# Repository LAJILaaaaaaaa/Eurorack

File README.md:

# Eurorack

## 模块尺寸规范
[01] [物理规格参考链接_doepfer](https://www.doepfer.de/a100_man/a100m_e.htm)  
[02] [物理规格参考链接_intellijel](https://intellijel.com/support/1u-technical-specifications/)

## 信号和电压
[电气规格参考链接](https://www.doepfer.de/a100_man/a100t_e.htm)  

### 音频信号  
>通常在10Vpp范围内（从-5V到+5V）。  

### 控制电压  
>由LFO和ADSR等调制源产生，LFO通常从-2.5 V到+2.5 V（5 Vpp），ADSR从0 V到+8 V。

### 触发电压  
>触发器、门或时钟信号，启动过程或功能，是矩形信号，典型电压电平为0/+5 V。在触发应用程序的情况下，通常是用于触发事件的信号的上升边缘。  

## 常用网站

### 模块制造商
- [makenoise](https://www.makenoisemusic.com)
- [instruo](https://www.instruomodular.com)
- [4ms](https://4mscompany.com)
- [mutable-instruments](https://pichenettes.github.io/mutable-instruments-documentation/)
- [busycircuits](https://busycircuits.com)
- [intellijel](https://intellijel.com)
- [expert-sleepers](https://www.expert-sleepers.co.uk)
- [befaco](https://www.befaco.org)
- [Der Mann mit der Maschine](https://shop.dermannmitdermaschine.de) 
- [antumbra](https://www.antumbra.eu)
- [QU-Bit](https://www.qubitelectronix.com/shop)
- [2HP](https://www.twohp.com/modules)
- [musicthing](https://www.musicthing.co.uk)
- [abyssdevices](https://abyssdevices.com)
- [monome](https://monome.org)

### 其他
- [thonk](https://www.thonk.co.uk)
- [modulargrid](https://modulargrid.net)
- [mouser](https://www.mouser.cn)

## 开发者套件
开发者套件的目的是将Eurorack中常用的电路模块化，方便Eurorack开发者们在面包板上进行电路实验。
### [PJ301M-12]()
> 单声道音频输入模块

### [PJ301BM]()
> 单声道音频输入模块

### [KEY_LED]()
> 带led灯的轻触开关模块  

### [KEY]()
> 轻触开关模块

### [LED]()
> LED灯模块

### [ENCODER]()
> 编码器模块

## 常用电路
- ne555时钟发生电路  
- 白噪声发生电路  
- 粉色噪声发生电路
- 采样保持电路  
- 电压比较器电路  
- 门转触发电路  
- 触发转门电路  
- 随机门发生器  
- 门随机跳过电路  
- AR包络发生器电路
- 随机电压发生电路

### LED灯光电路
1. 三极管
2. lm321运算放大器
3. 单led
4. 双led
5. rgb

### 运算放大器电路
1. 同相比例放大
2. 反相比例放大
3. 加法器
4. 电压跟随器

## 硬件驱动库
- OLED
- Key
- Encoder
- LED
- ADC
- DAC
- CAP1214电容触摸
- MAX7219数码管驱动

## 模拟电路
- multisim电路仿真

## PCB绘制
Kicad
- PCB艺术外观

## 合成器电路
### 参考网站

## DSP算法

## 常用开发板
- Stm32
  - f103c8t6
  - f411c8t6
- 树莓派
  - pico
  - 5
  - 4B+
- Arduino
  - nano
  - Uno R4

## 常用硬件
- 基础
  - 电阻
  - 电容  
  - 二极管
    - 1N4148高速开关二极管
    - 肖特基二极管
      - 1N5819HW
      - BAT54SLT1G双肖特基二极管
  - NPN三极管
    - MMBT3904
  - LDO
    - LM1117
    - MCP1703 LDO Vref
  - 磁珠
- 控制
  - 按键
  - 电位器
  - 编码器
- 显示
  - LED灯
  - OLED显示器
    - 0.96英寸（驱动SSD1306）
    - 1.29英寸（驱动CH1115）
    - 1.3英寸
    - 1.54英寸（驱动SSD1306）
    - 2.7英寸
- 输入输出
  - 3.5mm单声道插座
  - type-c插座
- 连接
  - 2.54排针排母
  - 1.27排针排母
  - 跳线帽
  - 11mm，m2铜柱
- 运算放大器
  - TL072
  - TL074
  - MCP6002 R2R
  - MCP6004 R2R
  - OPA4171 四运放
  - OPA2171 双运放
  - LM324 四运放
- ADC
  - ADS1115
- DAC
  - WM8731
  - DAC8564
  - DAC128S085
- 其他
  - LM4040
  - CD4051
  - 74hc595 移位寄存器
  - 74AHCT1G125
  - MAX7219 数码管驱动

## 开源模块存储库

> 存储一些开源的模块资料，防止丢失

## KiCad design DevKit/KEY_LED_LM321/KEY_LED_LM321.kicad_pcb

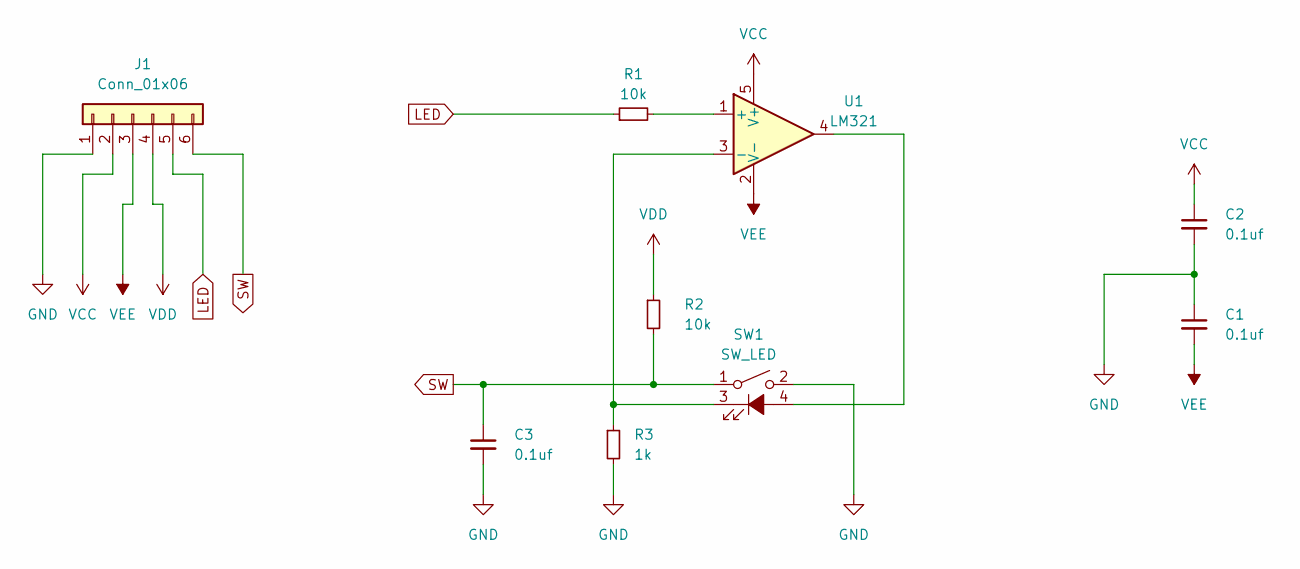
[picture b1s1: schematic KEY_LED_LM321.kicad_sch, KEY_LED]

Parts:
C1, C2, C3: 0.1uf; C_0603_1608Metric
J1: Conn_01x06; PinHeader_1x06_P2.54mm_Vertical
R1, R2: 10k; R_0603_1608Metric
R3: 1k; R_0603_1608Metric
SW1: SW_LED; Button_LED
U1: LM321; SOT-23-5

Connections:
GND: C1.1, C2.2, C3.2, J1.1, R3.2, SW1.2
LED: J1.5, R1.1
unnamed: SW1.4 (A), U1.4
unnamed: R3.1, SW1.3 (K), U1.3 (-)
unnamed: R1.2, U1.1 (+)
SW: C3.1, J1.6, R2.2, SW1.1
VCC: C2.1, J1.2, U1.5 (V+)
VDD: J1.4, R2.1
VEE: C1.2, J1.3, U1.2 (V-)

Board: 2 copper layers, 9 parts (8 on the bottom side), 9 nets, no tracks yet.

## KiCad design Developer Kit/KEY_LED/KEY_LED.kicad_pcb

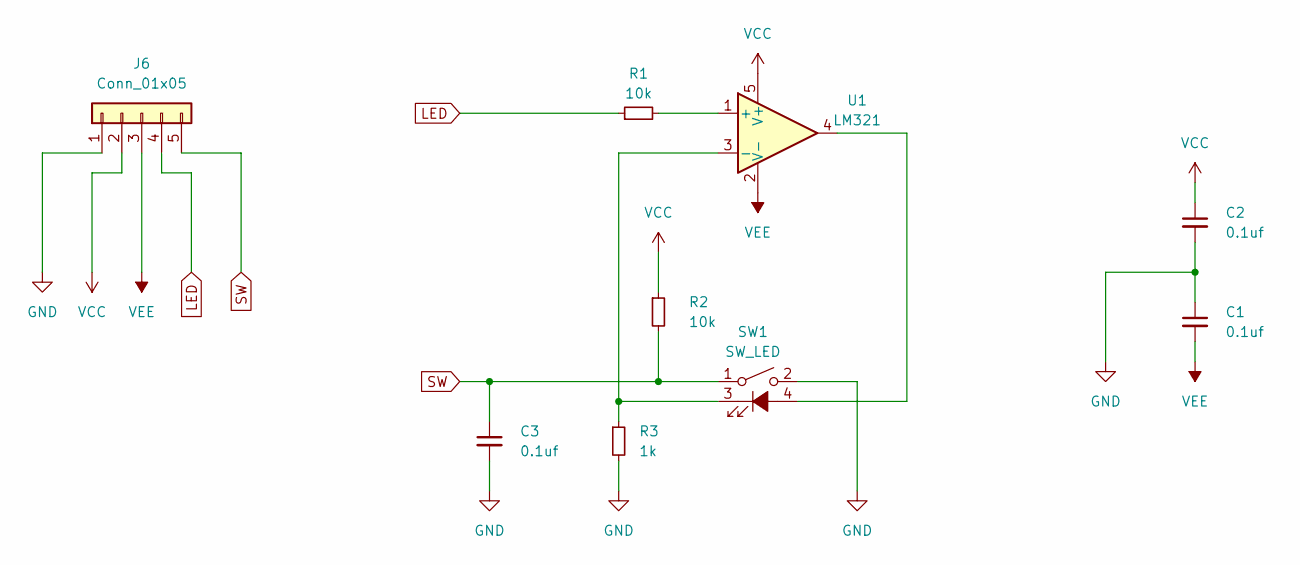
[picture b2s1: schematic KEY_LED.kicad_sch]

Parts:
C1, C2, C3: 0.1uf; C_0603_1608Metric
J6: Conn_01x05; PinHeader_1x05_P2.54mm_Vertical
R1, R2: 10k; R_0603_1608Metric
R3: 1k; R_0603_1608Metric
SW1: SW_LED; Button_LED
U1: LM321; SOT-23-5

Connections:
GND: C1.1, C2.2, C3.2, J6.1, R3.2, SW1.2
LED: J6.4, R1.1
unnamed: SW1.4 (A), U1.4
unnamed: R3.1, SW1.3 (K), U1.3 (-)
unnamed: R1.2, U1.1 (+)
SW: C3.1, J6.5, R2.2, SW1.1
VCC: C2.1, J6.2, R2.1, U1.5 (V+)
VEE: C1.2, J6.3, U1.2 (V-)

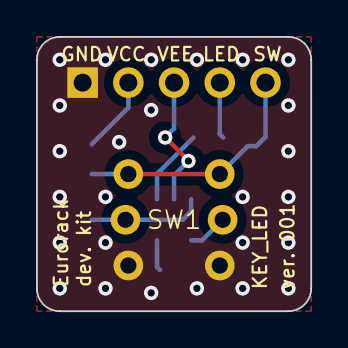
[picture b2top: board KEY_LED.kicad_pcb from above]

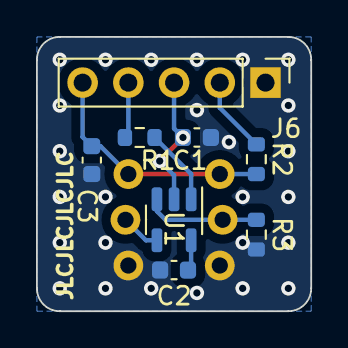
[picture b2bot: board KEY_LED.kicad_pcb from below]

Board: 2 copper layers, 15.2 x 15.2 mm, 9 parts (8 on the bottom side), 8 nets.

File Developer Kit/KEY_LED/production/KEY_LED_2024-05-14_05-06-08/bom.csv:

Designator,Footprint,Quantity,Value,LCSC Part #
"C1, C2, C3",0603,3,0.1uf,
J6,PinHeader_1x05_P2.54mm_Vertical,1,Conn_01x05,
"R1, R2",0603,2,10k,
R3,0603,1,1k,
SW1,Button_LED,1,SW_LED,
U1,SOT-23-5,1,LM321,

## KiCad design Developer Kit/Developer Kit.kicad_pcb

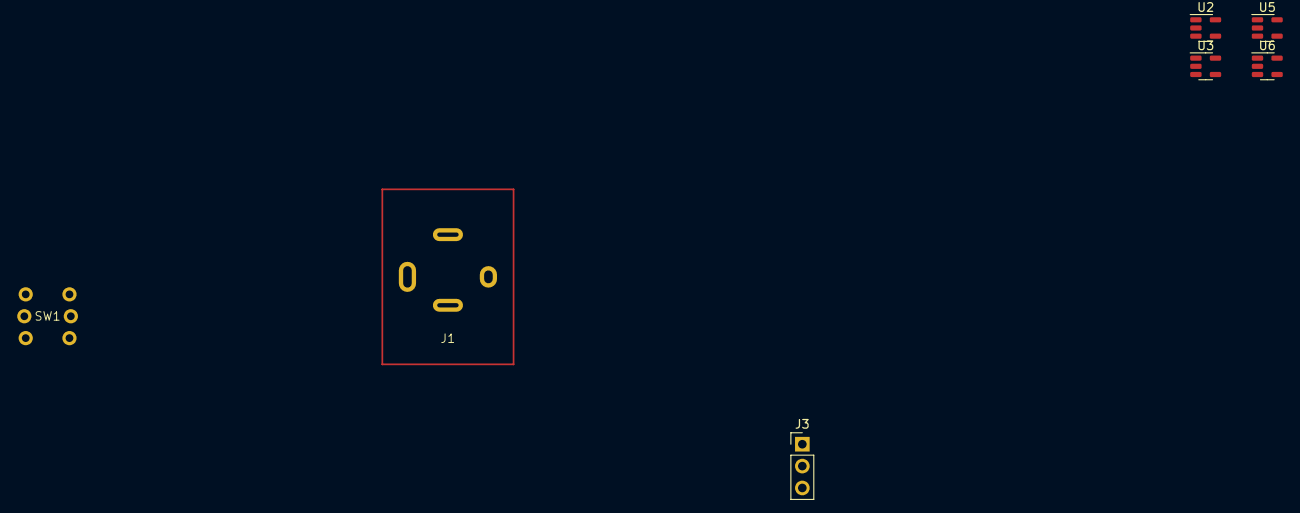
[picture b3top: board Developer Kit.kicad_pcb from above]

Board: 2 copper layers, 7 parts (0 on the bottom side), 4 nets, no tracks yet.

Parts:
J1: PJ-301BM
J3: Conn_01x03; PinHeader_1x03_P2.54mm_Vertical
SW1: SW_LED; Button_LED
U2, U3, U5, U6: LM321; SOT-23-5

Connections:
unnamed: U6.3 (-), U6.4
VCC: J3.1, U5.5 (V+), U6.5 (V+)
VEE: U5.2 (V-), U6.2 (V-)
signal: U5.1 (+), U6.1 (+)

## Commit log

2024-05-06 第一次提交
2024-05-07 日常更新
2024-05-13 添加了KEY_LED开发者套件，这是一个带有led灯带轻触开关模块
2024-05-13 添加了开发者套件说明
2024-05-13 描述修改
2024-06-25 笔记更新
2024-10-09 更新目录测试
